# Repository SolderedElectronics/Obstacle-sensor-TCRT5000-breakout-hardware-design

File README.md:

# Obstacle sensor TCRT5000 breakout Hardware Design

## About the Product

|  |
| :----------------------------------------------------------: |
| [Buy Obstacle sensor TCRT5000 breakout](https://www.solde.red/333012) |

Obstacle sensor, based on TCRT5000, uses infrared diode and photo-receiver to detect obstacle in front of it – emitted light just reflects back to the sensor. Onboard, you’ll find voltage comparator, so just by adjusting the potentiometer, the board gives digital output. There’s LED DO onboard to show the current digital output status. There’s analog output as well, in case you need it. Sensor works particularly well for line-following purposes on small robots.

---

## Repository Contents

This repository contains all design files for Obstacle sensor TCRT5000 breakout, organized as follows:

- **`CAD` folder**: Contains KiCAD design files, including:
  - Schematics
  - PCB layout
  - Panel PCB layout
  - Source 3D files in Fusion360, if any
  - All files are sorted by version with a detailed change log.
- **`OUTPUTS` folder**: Includes all production-ready files, such as:
  - Bill of Materials (BOM) and interactive BOM (iBOM)
  - PDF versions of schematics
  - 3D `.step` file of the board
  - 3D-printable models
  - Gerber files for PCB manufacturing
  - Image of the pinout of the board
  - Product image
  - Compliance, legal and generic sales documents

Refer to the `Change Log` in the CAD folder for details about updates between versions.

---

## Learn More About the Product

Beyond the repository, explore the following resources:

### Soldered Verify

The **Soldered Verify** system ensures every board you purchase from Soldered is fully functional. It also provides access to exclusive test data for your product. To get started, find the unique Soldered Verify ID on your product's packaging and enter the ID on the [Soldered Verify page](https://soldered.com/verify/) to access test results and additional product details.

### Soldered Community

Soldered Community is your go-to place for technical support. Our engineers track and answer all questions posted there, and it’s a great space for the maker community. Get answers to your questions and solutions for your challenges at [Soldered Community](https://soldered.com/community).

### solde.red

solde.red is an ultimate URL shortener and information hub. Access it by typing solde.red/ followed by your product SKU, e.g., [solde.red/333000](https://solde.red/333000), to find getting-started guides, datasheets, open-source hardware and software files, certifications, images, pinouts, and more. Read more about the shortener [here](https://solde.red/info/).

---

## Contributing

Contributions are welcome! Here’s how you can get involved:

- Submit pull requests to enhance the design or fix issues.
- Report bugs or problems by opening an issue.

We encourage community collaboration to make this product even better.

---

## About Soldered

[Soldered for Makers](https://soldered.com) specializes in designing and manufacturing electronic products tailored for enthusiasts, ranging from hobbyists to professionals. Our portfolio includes electronic boards, sensors, and actuators that are widely utilized in fields such as microelectronics, mechatronics, robotics, programming, and IoT. Every product we offer is designed in-house and built upon open-source hardware and software platforms. Proudly certified and manufactured within the European Union, our catalog likely includes the product you need for your project.

We complement these products with comprehensive tutorials and manuals, product descriptions, schematics, programming codes, and project examples. Our round-the-clock [customer and technical support](https://soldered.com/community) is available for all our products, irrespective of the sales channel. Soldered’s success and services reflect our maker community’s unwavering [trust](https://www.trustpilot.com/review/soldered.com), for which we are deeply grateful. Join our community and create using Soldered products.

---

## License

All Soldered open-source hardware (OSH) is under The TAPR Open Hardware License. Read more in the LICENSE file located in this repository.

**Disclaimer:**

No warranty - all designs in this repository are distributed in the hope that they will be useful, but without any warranty. They are provided "AS IS", therefore without warranty of any kind, either expressed or implied. The entire quality and performance of what you do with the contents of this repository are your responsibility. In no event Soldered Electronics will be liable for your damages, or losses, including any general, special, incidental, or consequential damage arising out of the use or inability to use the contents of this repository. 

---

## Have fun!

Thank you for your support from your fellow makers at Soldered Electronics.

Happy Making!

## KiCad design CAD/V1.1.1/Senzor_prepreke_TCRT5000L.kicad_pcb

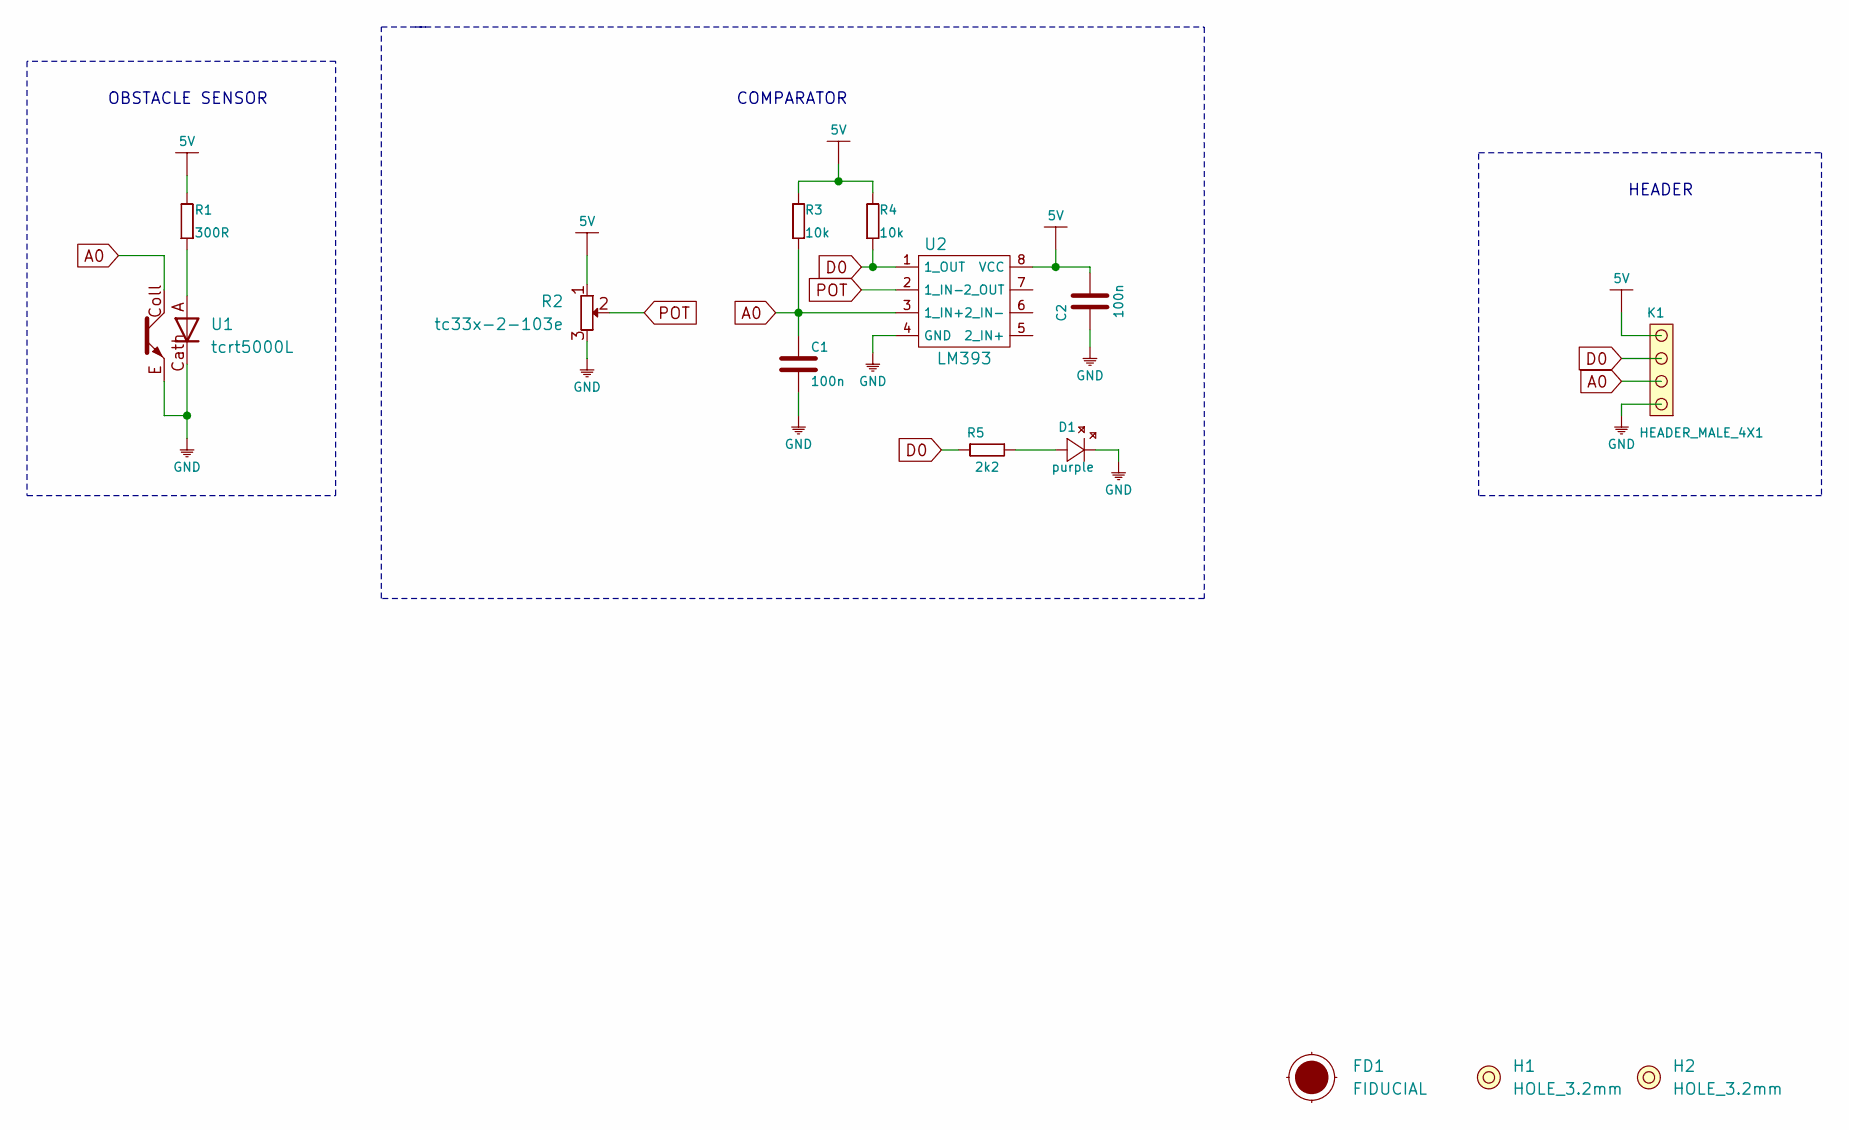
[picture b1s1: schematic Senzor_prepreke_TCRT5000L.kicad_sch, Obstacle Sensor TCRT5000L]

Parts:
C1, C2: 100n; 0603C
D1: purple; 0402LED
FD1: FIDUCIAL; FIDUCIAL_23
H1, H2: HOLE_3.2mm
K1: HEADER_MALE_4X1
R1: 300R; 0603R
R2: tc33x-2-103e
R3, R4: 10k; 0603R
R5: 2k2; 0402R
U1: tcrt5000L; TCRT5000L
U2: LM393; SOIC−8

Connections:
5V: C2.2, K1.4, R1.2, R2.1, R3.2, R4.2, U2.8 (VCC)
A0: C1.2, K1.2, R3.1, U1.Coll, U2.3 (1_IN+)
D0: K1.3, R4.1, R5.1, U2.1 (1_OUT)
GND: C1.1, C2.1, D1.2 (K), K1.1, R2.3, U1.Cath, U1.E, U2.4 (GND)
unnamed: D1.1 (A), R5.2
unnamed: R1.1, U1.A
POT: R2.2, U2.2 (1_IN-)

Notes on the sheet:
COMPARATOR
HEADER
OBSTACLE SENSOR

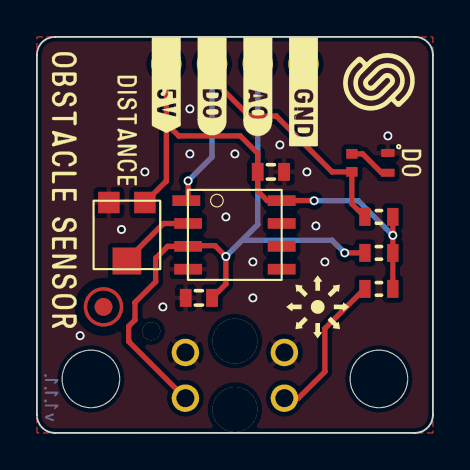
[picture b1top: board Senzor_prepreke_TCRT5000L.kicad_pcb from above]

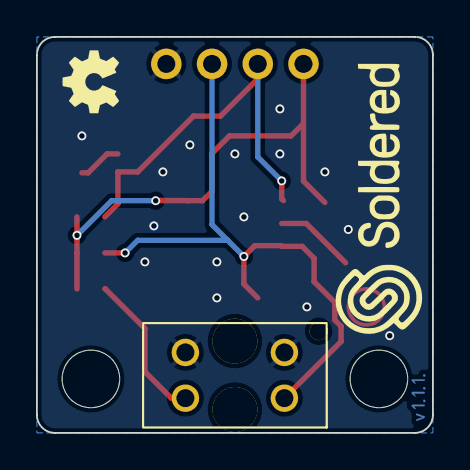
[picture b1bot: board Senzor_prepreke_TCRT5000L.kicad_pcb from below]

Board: 2 copper layers, 22.0 x 22.0 mm, 14 parts (2 on the bottom side), 7 nets.

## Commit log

2022-08-06 Updating open source files.
